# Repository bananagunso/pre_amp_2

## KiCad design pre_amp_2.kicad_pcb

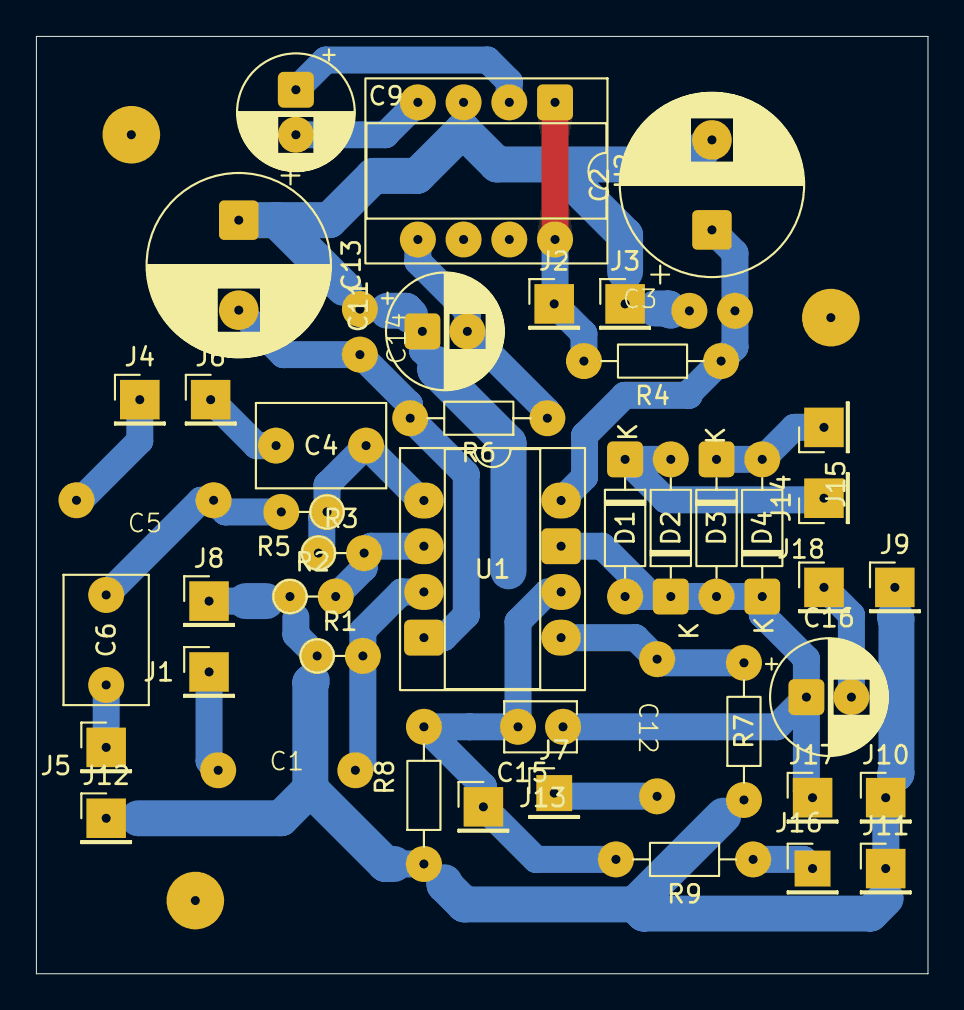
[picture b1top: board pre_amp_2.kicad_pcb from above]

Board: 2 copper layers, 49.5 x 52.1 mm, 49 parts (0 on the bottom side), 24 nets.

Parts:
C1, C5, C12: 0.1u; 11.6_7.0_p7.5
C2, C13: 1000u; CP_Radial_D10.0mm_P5.00mm
C3, C14: 0.1u; 5.3_2.5_p2.5
C4: 220p; C_Rect_L7.0mm_W4.5mm_P5.00mm
C6: 0.047u; C_Rect_L7.0mm_W4.5mm_P5.00mm
C9, C11, C16: 10u; CP_Radial_D6.3mm_P2.50mm
C15: 47p; C_Disc_D3.8mm_W2.6mm_P2.50mm
D1, D2: 1N4148; D_DO-35_SOD27_P7.62mm_Horizontal
D3, D4: 1N60; D_DO-35_SOD27_P7.62mm_Horizontal
H1, H2, H3: MountingHole; MountingHole_3.2mm_M3
J1: IN; PinHeader_1x01_P2.54mm_Vertical
J2: Vin; PinHeader_1x01_P2.54mm_Vertical
J3: GND; PinHeader_1x01_P2.54mm_Vertical
J4: VR2_2; PinHeader_1x01_P2.54mm_Vertical
J5: VR3_3; PinHeader_1x01_P2.54mm_Vertical
J6: VR1_3; PinHeader_1x01_P2.54mm_Vertical
J7: VR4_2; PinHeader_1x01_P2.54mm_Vertical
J8: GNDIN; PinHeader_1x01_P2.54mm_Vertical
J9: GNDOUT; PinHeader_1x01_P2.54mm_Vertical
J10: GND5_1; PinHeader_1x01_P2.54mm_Vertical
J11: GND5_3; PinHeader_1x01_P2.54mm_Vertical
J12: GND3_3; PinHeader_1x01_P2.54mm_Vertical
J13: SW2_3; PinHeader_1x01_P2.54mm_Vertical
J14: SW2_1; PinHeader_1x01_P2.54mm_Vertical
J15: SW2_4; PinHeader_1x01_P2.54mm_Vertical
J16: VR5_3; PinHeader_1x01_P2.54mm_Vertical
J17: VR5_1; PinHeader_1x01_P2.54mm_Vertical
J18: OUT; PinHeader_1x01_P2.54mm_Vertical
R1: 1M; R_Axial_DIN0204_L3.6mm_D1.6mm_P2.54mm_Vertical
R2: 10k; R_Axial_DIN0204_L3.6mm_D1.6mm_P2.54mm_Vertical
R3: 47k; R_Axial_DIN0204_L3.6mm_D1.6mm_P2.54mm_Vertical
R4, R6: 22; R_Axial_DIN0204_L3.6mm_D1.6mm_P7.62mm_Horizontal
R5: 100k; R_Axial_DIN0204_L3.6mm_D1.6mm_P2.54mm_Vertical
R7: 2.2M; R_Axial_DIN0204_L3.6mm_D1.6mm_P7.62mm_Horizontal
R8, R9: 1k; R_Axial_DIN0204_L3.6mm_D1.6mm_P7.62mm_Horizontal
U1: TL072; CERDIP-8_W7.62mm_SideBrazed_Socket
U2: TC1044S; CERDIP-8_W7.62mm_SideBrazed_Socket

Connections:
GND: C2.2, C3.2, C11.1, C13.1, C14.2, J3.1, U2.3 (GND)
GND2: J8.1, J9.1, J10.1, J11.1, J12.1, R1.1, R2.1, R7.1, R8.1
unnamed: C4.1, R3.1, R5.1, U1.1
unnamed: C5.1, C6.1, R5.2
unnamed: C15.1, C16.1, D1.2 (A), D2.1 (K), D3.2 (A), D4.1 (K), J17.1, U1.7
unnamed: D1.1 (K), D2.2 (A), J14.1
unnamed: D3.1 (K), D4.2 (A), J15.1
unnamed: C1.1, J1.1
unnamed: J2.1, R4.2, U2.1 (BOOST), U2.8 (V+)
unnamed: C5.2, J4.1
unnamed: C6.2, J5.1
unnamed: C4.2, J6.1
unnamed: C12.1, J7.1
unnamed: C15.2, J13.1, R8.2, R9.2, U1.6 (-)
unnamed: J16.1, R9.1
unnamed: C16.2, J18.1
unnamed: C1.2, R1.2, U1.3 (+)
unnamed: R2.2, R3.2, U1.2 (-)
unnamed: C12.2, R7.2, U1.5 (+)
unnamed: C2.1, C3.1, R4.1, U1.8 (V+)
unnamed: C13.2, C14.1, R6.2, U1.4 (V-)
unnamed: C9.1, U2.2 (CAP+)
unnamed: C9.2, U2.4 (CAP-)
unnamed: C11.2, R6.1, U2.5 (VOUT)

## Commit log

2026-02-28 チャージポンプの両電源とフェンダーのイコライザー回路
2026-03-01 配置修正
2026-03-01 LED用の抵抗を追加
2026-03-01 ドリル穴のサイズを修正
2026-03-02 配置を修正
2026-03-09 配置をやり直す
2026-03-10 電源と入力のGNDを分離して配置を修正
2026-03-10 パッドの大きさを大きくした
2026-03-10 配線の接続先を修正
2026-03-12 ICにパスコンを付けるためGND2を近づけた
2026-03-12 配線を修正
2026-03-21 入力部分が抵抗(GND)->コンデンサ->ICだったのをコンデンサ->抵抗(GND)->ICに変更。 (直流がICにたまってGNDに落ちず音が出なくなる)
2026-03-23 基板からつなぐボリュームの先を変更
2026-03-23 オペアンプのパスコンを基板上に配置しようとしたけど諦めて 裏に繋ぐ
2026-03-24 TC1044Sに変更
2026-03-27 67番ピンに330pを追加、ICパッケージのすぐ横に付ける
2026-03-31 発振対策で初段の増幅率を上げて後段のボリュームと抵抗の値を調整
2026-04-01 R3を47kに変更、シールド線の網線をGNDに繋ぐ配線を追加。
2026-04-05 チャージポンプの抵抗と電解コンデンサを強化
